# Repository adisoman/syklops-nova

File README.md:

# syklops-nova
Syklops nova is a series of beginner friendly I2C extender boards for GPIOs. It makes complex multi-component work possible, even for MCUs with fewer GPIOs.

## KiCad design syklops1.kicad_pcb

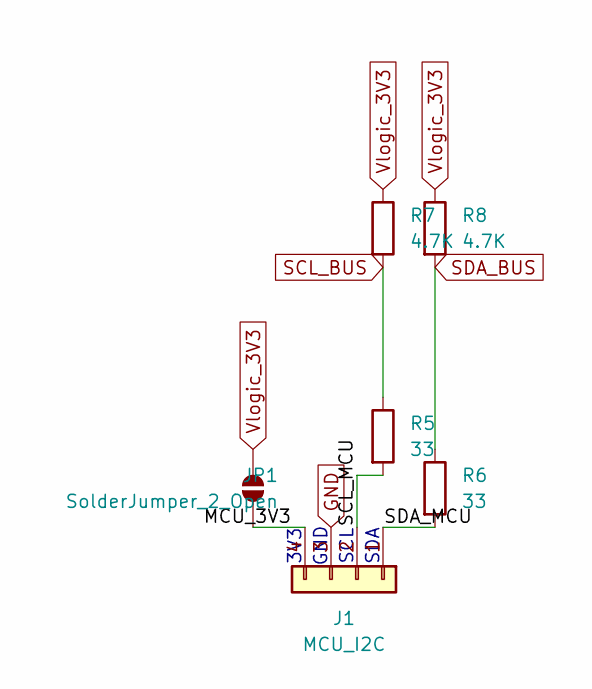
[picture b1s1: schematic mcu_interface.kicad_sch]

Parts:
J1: MCU_I2C; PinSocket_1x04_P2.54mm_Vertical; LCSC C5116530
JP1: SolderJumper_2_Open; SolderJumper-2_P1.3mm_Open_RoundedPad1.0x1.5mm
R5, R6: 33; R_0805_2012Metric; LCSC C17634
R7, R8: 4.7K; R_0805_2012Metric; LCSC C17673

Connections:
/MCU_interface/MCU_3V3: J1.4, JP1.1 (A)
/MCU_interface/SCL_MCU: J1.2, R5.2
/MCU_interface/SDA_MCU: J1.1, R6.2
GND: J1.3; also elsewhere on the board
SCL_BUS: R5.1, R7.2; also elsewhere on the board
SDA_BUS: R6.1, R8.2; also elsewhere on the board
Vlogic_3V3: JP1.2 (B), R7.1, R8.1; also elsewhere on the board

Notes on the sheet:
SDA
SCL
3V3
GND

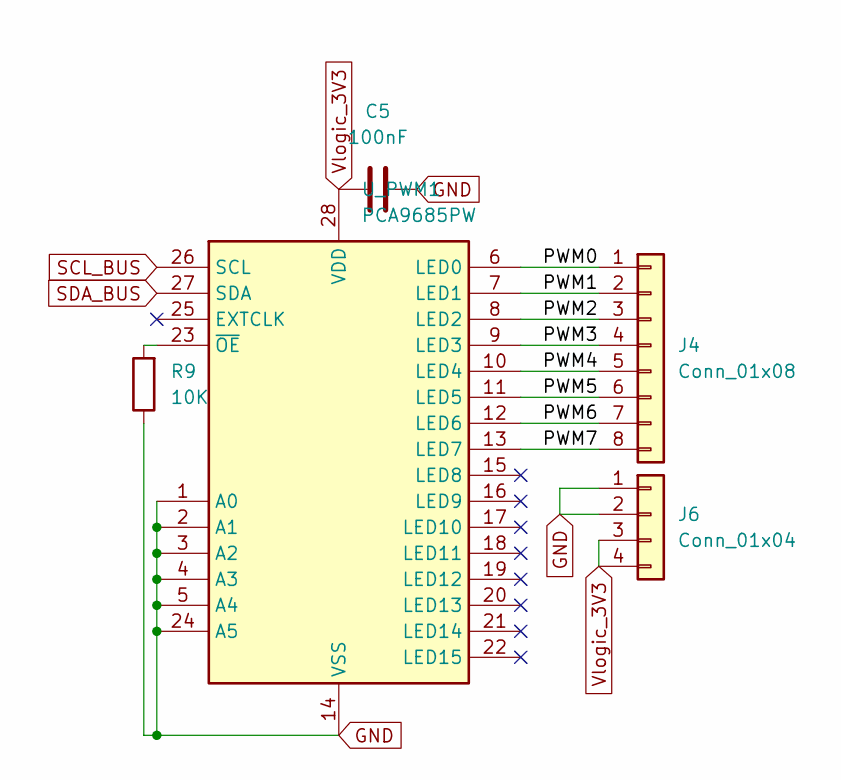
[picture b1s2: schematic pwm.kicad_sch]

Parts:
C5: 100nF; C_0805_2012Metric; LCSC C49678
J4: Conn_01x08; PinSocket_1x08_P2.54mm_Vertical; LCSC C18078131
J6: Conn_01x04; PinSocket_1x04_P2.54mm_Vertical; LCSC C5116530
R9: 10K; R_0805_2012Metric; LCSC C17414
U_PWM1: PCA9685PW; TSSOP-28_4.4x9.7mm_P0.65mm; LCSC C11628

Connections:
/PWM/PWM0: J4.1, U_PWM1.6 (LED0)
/PWM/PWM1: J4.2, U_PWM1.7 (LED1)
/PWM/PWM2: J4.3, U_PWM1.8 (LED2)
/PWM/PWM3: J4.4, U_PWM1.9 (LED3)
/PWM/PWM4: J4.5, U_PWM1.10 (LED4)
/PWM/PWM5: J4.6, U_PWM1.11 (LED5)
/PWM/PWM6: J4.7, U_PWM1.12 (LED6)
/PWM/PWM7: J4.8, U_PWM1.13 (LED7)
GND: C5.2, J6.1, J6.2, R9.1, U_PWM1.1 (A0), U_PWM1.2 (A1), U_PWM1.3 (A2), U_PWM1.4 (A3), U_PWM1.5 (A4), U_PWM1.14 (VSS), U_PWM1.24 (A5); also elsewhere on the board
unnamed: R9.2, U_PWM1.23 (~OE)
SCL_BUS: U_PWM1.26 (SCL); also elsewhere on the board
SDA_BUS: U_PWM1.27 (SDA); also elsewhere on the board
Vlogic_3V3: C5.1, J6.3, J6.4, U_PWM1.28 (VDD); also elsewhere on the board

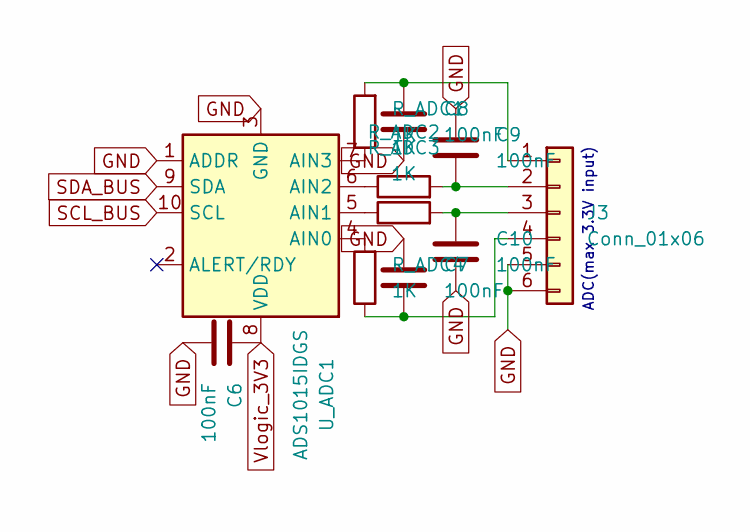
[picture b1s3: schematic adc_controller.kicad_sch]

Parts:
C6, C7, C8, C9, C10: 100nF; C_0805_2012Metric; LCSC C49678
J3: Conn_01x06; PinSocket_1x06_P2.54mm_Vertical; LCSC C40877
R_ADC1, R_ADC2, R_ADC3, R_ADC4: 1K; R_0805_2012Metric; LCSC C17513
U_ADC1: ADS1015IDGS; TSSOP-10_3x3mm_P0.5mm; LCSC C16581

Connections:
GND: C6.2, C7.1, C8.2, C9.1, C10.2, J3.5, J3.6, U_ADC1.1 (ADDR), U_ADC1.3 (GND); also elsewhere on the board
unnamed: C8.1, J3.1, R_ADC1.2
unnamed: C9.2, J3.2, R_ADC2.2
unnamed: C10.1, J3.3, R_ADC3.2
unnamed: C7.2, J3.4, R_ADC4.1
unnamed: R_ADC4.2, U_ADC1.4 (AIN0)
unnamed: R_ADC3.1, U_ADC1.5 (AIN1)
unnamed: R_ADC2.1, U_ADC1.6 (AIN2)
unnamed: R_ADC1.1, U_ADC1.7 (AIN3)
SCL_BUS: U_ADC1.10 (SCL); also elsewhere on the board
SDA_BUS: U_ADC1.9 (SDA); also elsewhere on the board
Vlogic_3V3: C6.1, U_ADC1.8 (VDD); also elsewhere on the board

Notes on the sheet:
ADC(max 3.3V input)

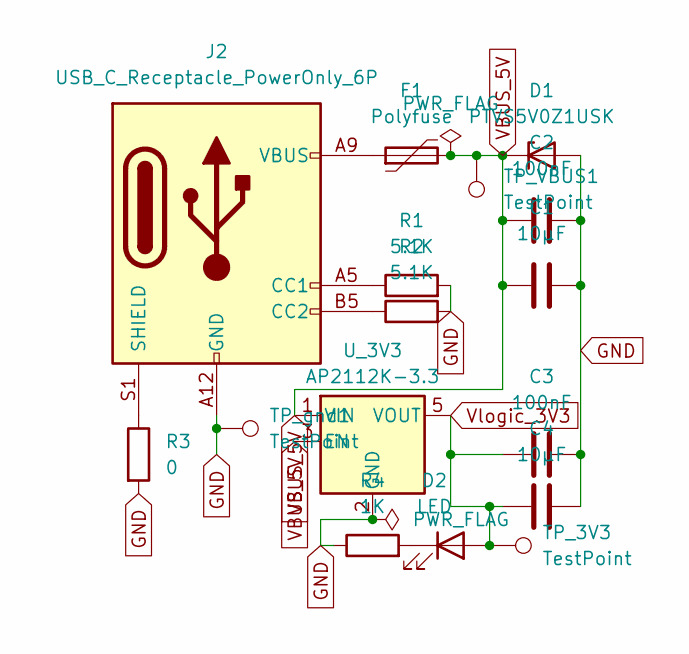
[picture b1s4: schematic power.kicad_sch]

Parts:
C1, C4: 10μF; C_0805_2012Metric; LCSC C15850
C2, C3: 100nF; C_0805_2012Metric; LCSC C49678
D1: PTVS5V0Z1USK; Nexperia_DSN1608-2_1.6x0.8mm; LCSC C85364
D2: LED; LED_0805_2012Metric; LCSC C2827270
F1: Polyfuse; Fuse_1206_3216Metric; LCSC C70059
J2: USB_C_Receptacle_PowerOnly_6P; USB_C_Receptacle_HRO_TYPE-C-31-M-17; LCSC C283540
R1, R2: 5.1K; R_0603_1608Metric; LCSC C23186
R3: 0; R_0805_2012Metric; LCSC C17477
R4: 1K; R_0805_2012Metric; LCSC C17604
TP_3V3: TestPoint; TestPoint_Pad_D1.5mm
TP_VBUS1: TestPoint; TestPoint_Pad_D1.5mm
TP_gnd1: TestPoint; TestPoint_Pad_D1.5mm
U_3V3: AP2112K-3.3; SOT-23-5; LCSC C51118

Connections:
GND: C1.2, C2.2, C3.2, C4.2, D1.2 (A), J2.A12 (GND), J2.B12 (GND), R1.2, R2.2, R3.2, R4.1, TP_gnd1.1, U_3V3.2 (GND); also elsewhere on the board
unnamed: D2.1 (K), R4.2
unnamed: F1.1, J2.A9 (VBUS), J2.B9 (VBUS)
unnamed: J2.A5 (CC1), R1.1
unnamed: J2.B5 (CC2), R2.1
unnamed: J2.S1 (SHIELD), R3.1
VBUS_5V: C1.1, C2.1, D1.1 (K), F1.2, TP_VBUS1.1, U_3V3.1 (VIN), U_3V3.3 (EN)
Vlogic_3V3: C3.1, C4.1, D2.2 (A), TP_3V3.1, U_3V3.5 (VOUT); also elsewhere on the board

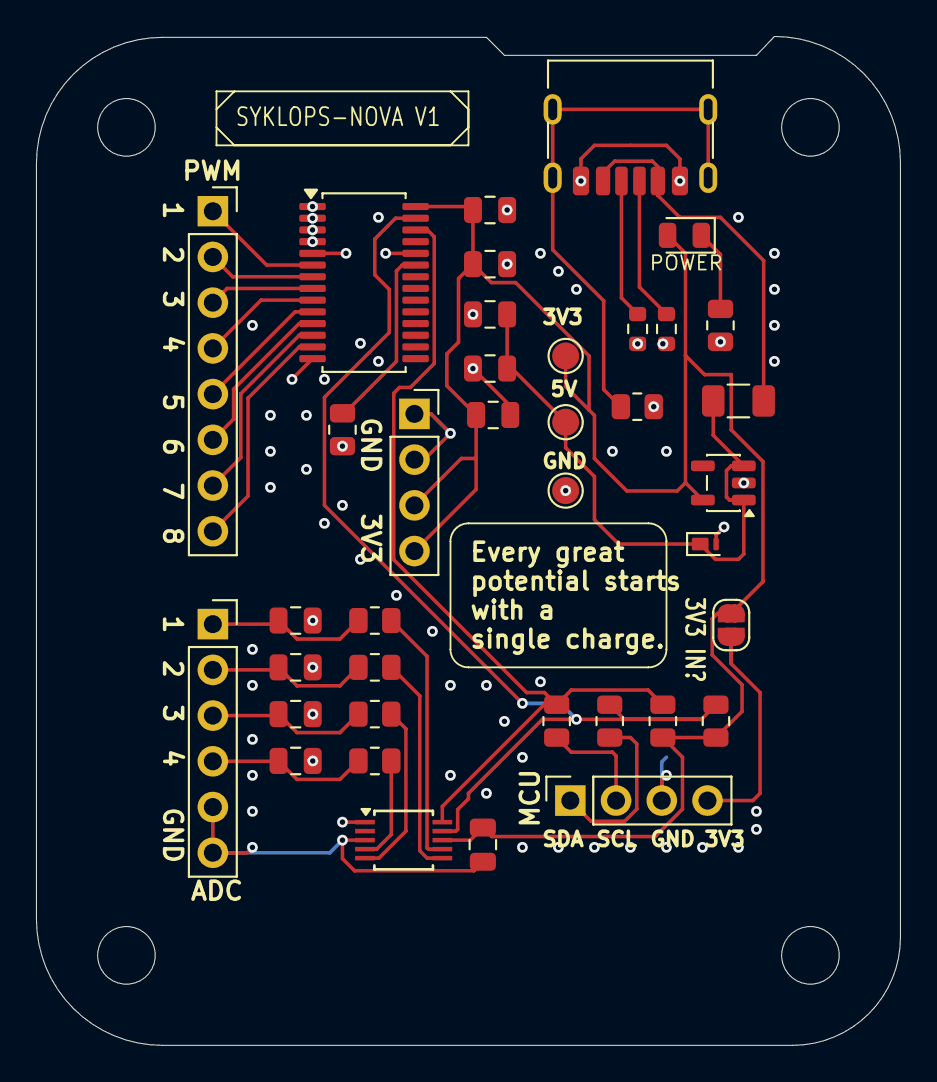
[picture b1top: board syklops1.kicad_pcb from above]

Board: 2 copper layers, 48.0 x 56.1 mm, 38 parts (0 on the bottom side), 30 nets.

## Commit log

2026-01-08 Add files via upload
    V1 : initial schematic with ADC expansion
2026-01-08 Add files via upload
    v1.2 : complete schematics with added footprints, PCB layout remaining
2026-01-09 Add files via upload
    v3 : all components added to PCB editor. no mounting holes yet.
2026-01-09 Add files via upload
    v3 : almost complete PCB layout, one common GND instance missing, USB-C footprint without BOM
2026-01-10 Add files via upload
    V4 : completed and working PCB. now zero DRC errors yet. room for refinement but working.
2026-01-10 Add files via upload
    V4 : full and final v1.1. Working schematics. Working PCB layout, zero ERC and DRC errors and warnings(except for cosmetic ones).
2026-01-10 Add files via upload
    V5 : complete finish for v1, directly to-the-fab design.
2026-01-16 Add MIT License to the project
